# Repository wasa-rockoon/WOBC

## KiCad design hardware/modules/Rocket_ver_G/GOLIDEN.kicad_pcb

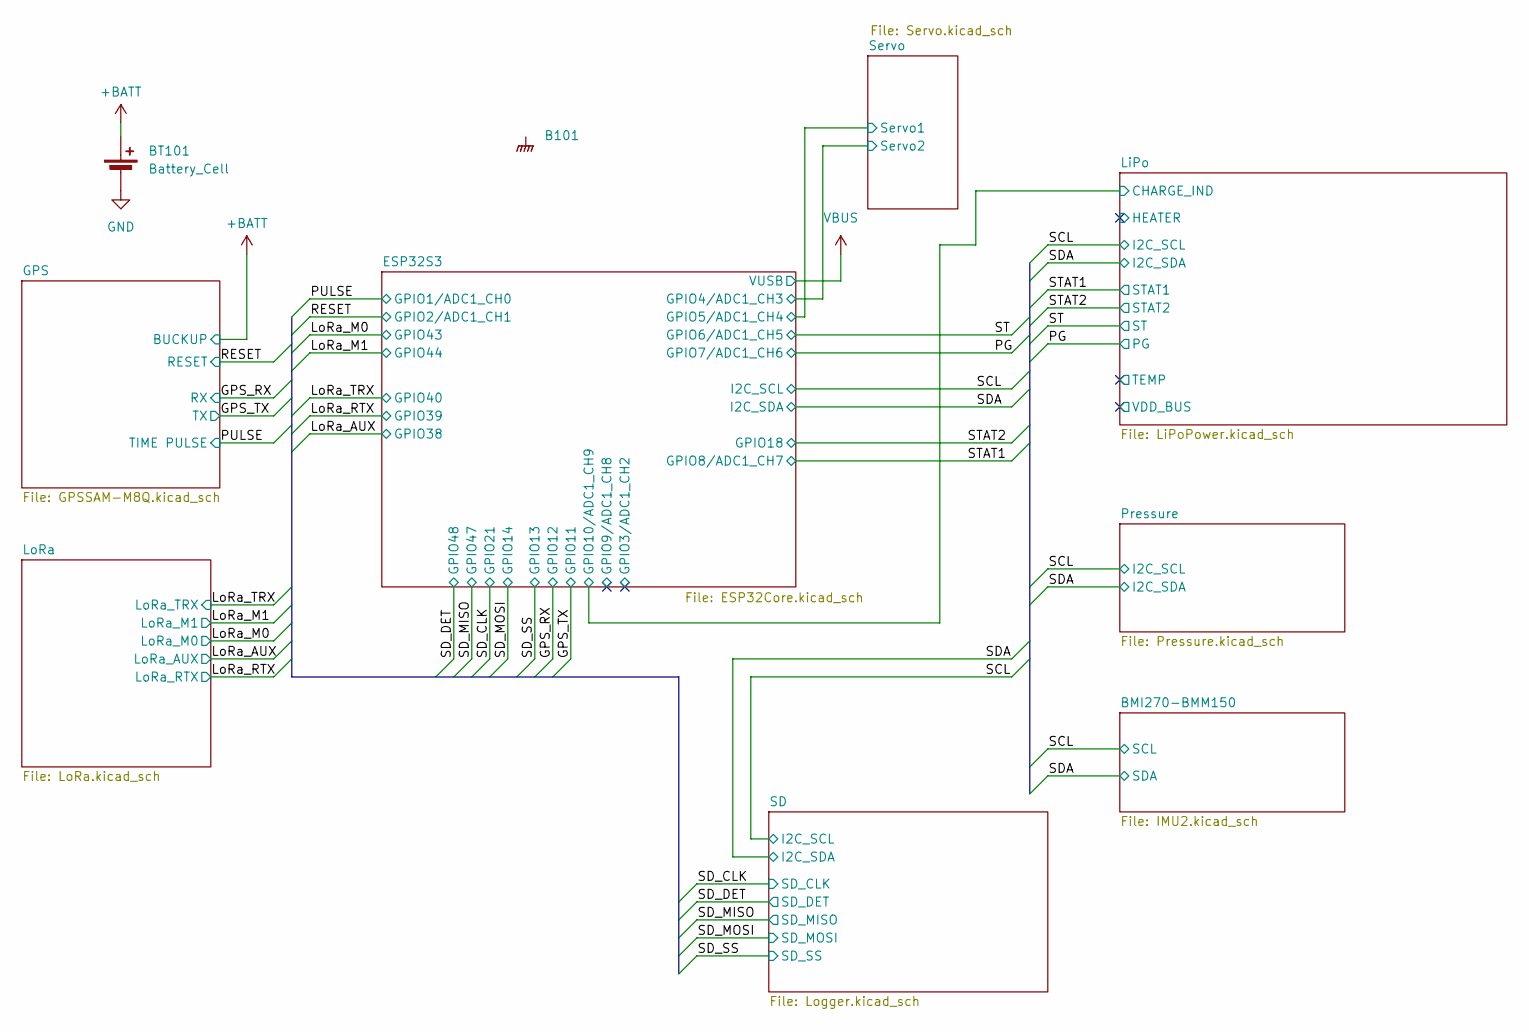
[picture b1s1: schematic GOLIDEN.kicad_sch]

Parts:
B101: Board_1U_40x120_for_Rocket
BT101: Battery_Cell; cr1220

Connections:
+BATT: BT101.1 (+); also elsewhere on the board
GND: B101.GND, BT101.2 (-); also elsewhere on the board

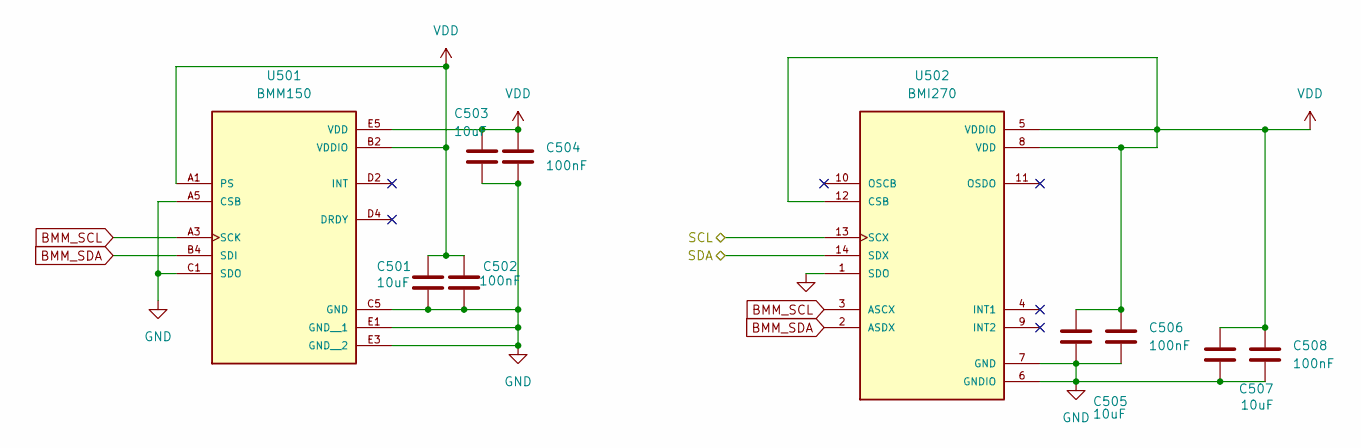
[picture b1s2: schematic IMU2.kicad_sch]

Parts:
C501, C503, C505, C507: 10uF; C_0603_1608Metric
C502, C504, C506, C508: 100nF; C_0402_1005Metric
U501: BMM150; XDCR_BMM150
U502: BMI270; XDCR_BMI270

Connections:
/SCL: U502.13 (SCX); also elsewhere on the board
/SDA: U502.14 (SDX); also elsewhere on the board
BMM_SCL: U501.A3 (SCK), U502.3 (ASCX)
BMM_SDA: U501.B4 (SDI), U502.2 (ASDX)
GND: C501.2, C502.2, C503.2, C504.2, C505.2, C506.2, C507.2, C508.2, U501.A5 (CSB), U501.C1 (SDO), U501.C5 (GND), U501.E1 (GND__1), U501.E3 (GND__2), U502.1 (SDO), U502.6 (GNDIO), U502.7 (GND); also elsewhere on the board
VDD: C501.1, C502.1, C503.1, C504.1, C505.1, C506.1, C507.1, C508.1, U501.A1 (PS), U501.B2 (VDDIO), U501.E5 (VDD), U502.5 (VDDIO), U502.8 (VDD), U502.12 (CSB); also elsewhere on the board

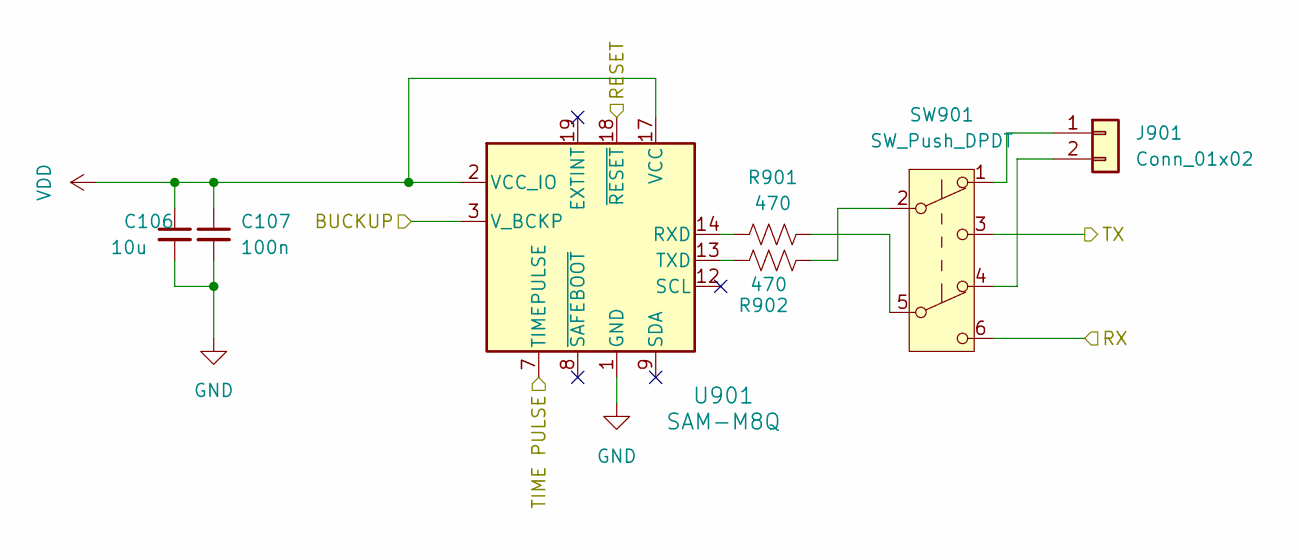
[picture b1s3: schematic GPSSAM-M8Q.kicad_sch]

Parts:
C106: 10u; C_0603_1608Metric; LCSC C96446
C107: 100n; C_0402_1005Metric; LCSC C1525
J901: Conn_01x02; PinHeader_1x02_P2.54mm_Vertical
R901, R902: 470; R_0402_1005Metric
SW901: SW_Push_DPDT; IS-2245S-G
U901: SAM-M8Q; ublox_SAM-M8Q

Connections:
+BATT: U901.3 (V_BCKP); also elsewhere on the board
/GPS_RX: SW901.6 (C); also elsewhere on the board
/GPS_TX: SW901.3 (C); also elsewhere on the board
/PULSE: U901.7 (TIMEPULSE); also elsewhere on the board
/RESET: U901.18 (~RESET); also elsewhere on the board
GND: C106.2, C107.2, U901.1 (GND), U901.4 (GND), U901.5 (GND), U901.6 (GND), U901.10 (GND), U901.11 (GND), U901.15 (GND), U901.16 (GND), U901.20 (GND); also elsewhere on the board
unnamed: J901.1, SW901.1 (A)
unnamed: J901.2, SW901.4 (A)
unnamed: R901.2, SW901.5 (B)
unnamed: R902.2, SW901.2 (B)
unnamed: R901.1, U901.14 (RXD)
unnamed: R902.1, U901.13 (TXD)
VDD: C106.1, C107.1, U901.2 (VCC_IO), U901.17 (VCC); also elsewhere on the board

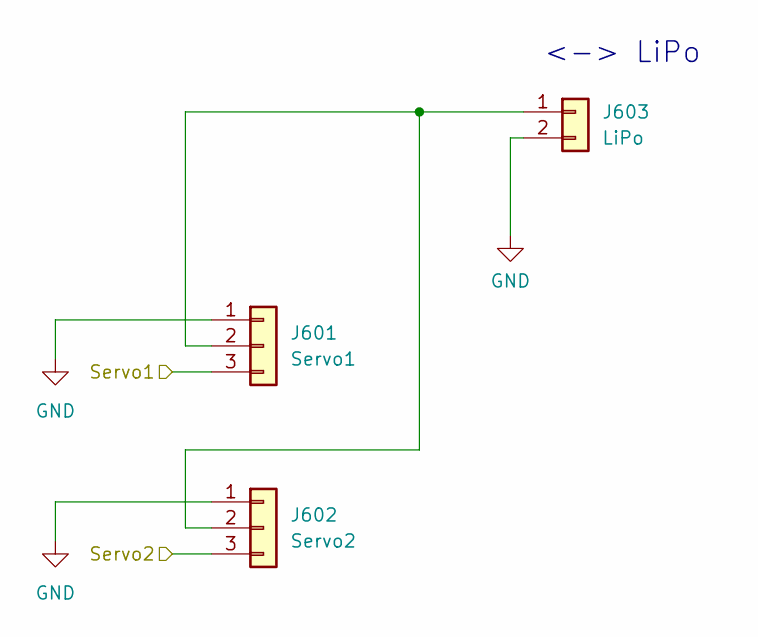
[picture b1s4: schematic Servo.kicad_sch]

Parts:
J601: Servo1; Harwin_M20-89003xx_1x03_P2.54mm_Horizontal
J602: Servo2; Harwin_M20-89003xx_1x03_P2.54mm_Horizontal
J603: LiPo; JST_PH_S2B-PH-K_1x02_P2.00mm_Horizontal

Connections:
/ESP32S3/GPIO4/ADC1_CH3: J602.3; also elsewhere on the board
/ESP32S3/GPIO5/ADC1_CH4: J601.3; also elsewhere on the board
GND: J601.1, J602.1, J603.2; also elsewhere on the board
unnamed: J601.2, J602.2, J603.1

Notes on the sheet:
<-> LiPo

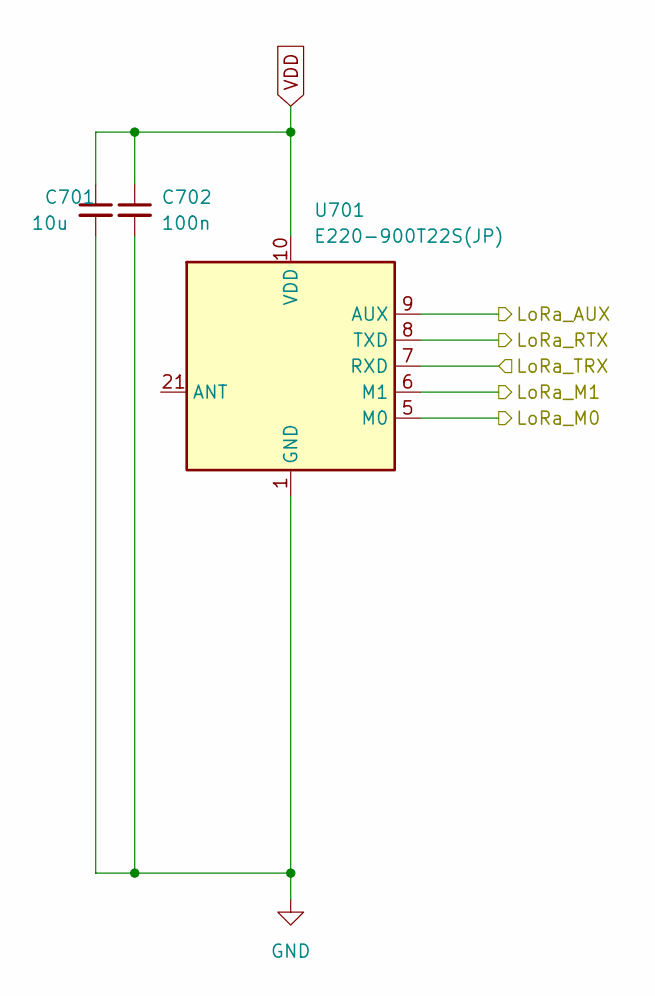
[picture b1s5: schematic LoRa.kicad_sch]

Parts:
C701: 10u; C_0603_1608Metric; LCSC C96446
C702: 100n; C_0402_1005Metric; LCSC C1525
U701: E220-900T22S(JP)

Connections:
/LoRa_AUX: U701.9 (AUX); also elsewhere on the board
/LoRa_M0: U701.5 (M0); also elsewhere on the board
/LoRa_M1: U701.6 (M1); also elsewhere on the board
/LoRa_RTX: U701.8 (TXD); also elsewhere on the board
/LoRa_TRX: U701.7 (RXD); also elsewhere on the board
GND: C701.2, C702.2, U701.1 (GND), U701.2 (GND), U701.3 (GND), U701.4 (GND), U701.11 (GND), U701.13 (GND), U701.19 (GND), U701.20 (GND), U701.22 (GND); also elsewhere on the board
VDD: C701.1, C702.1, U701.10 (VDD); also elsewhere on the board

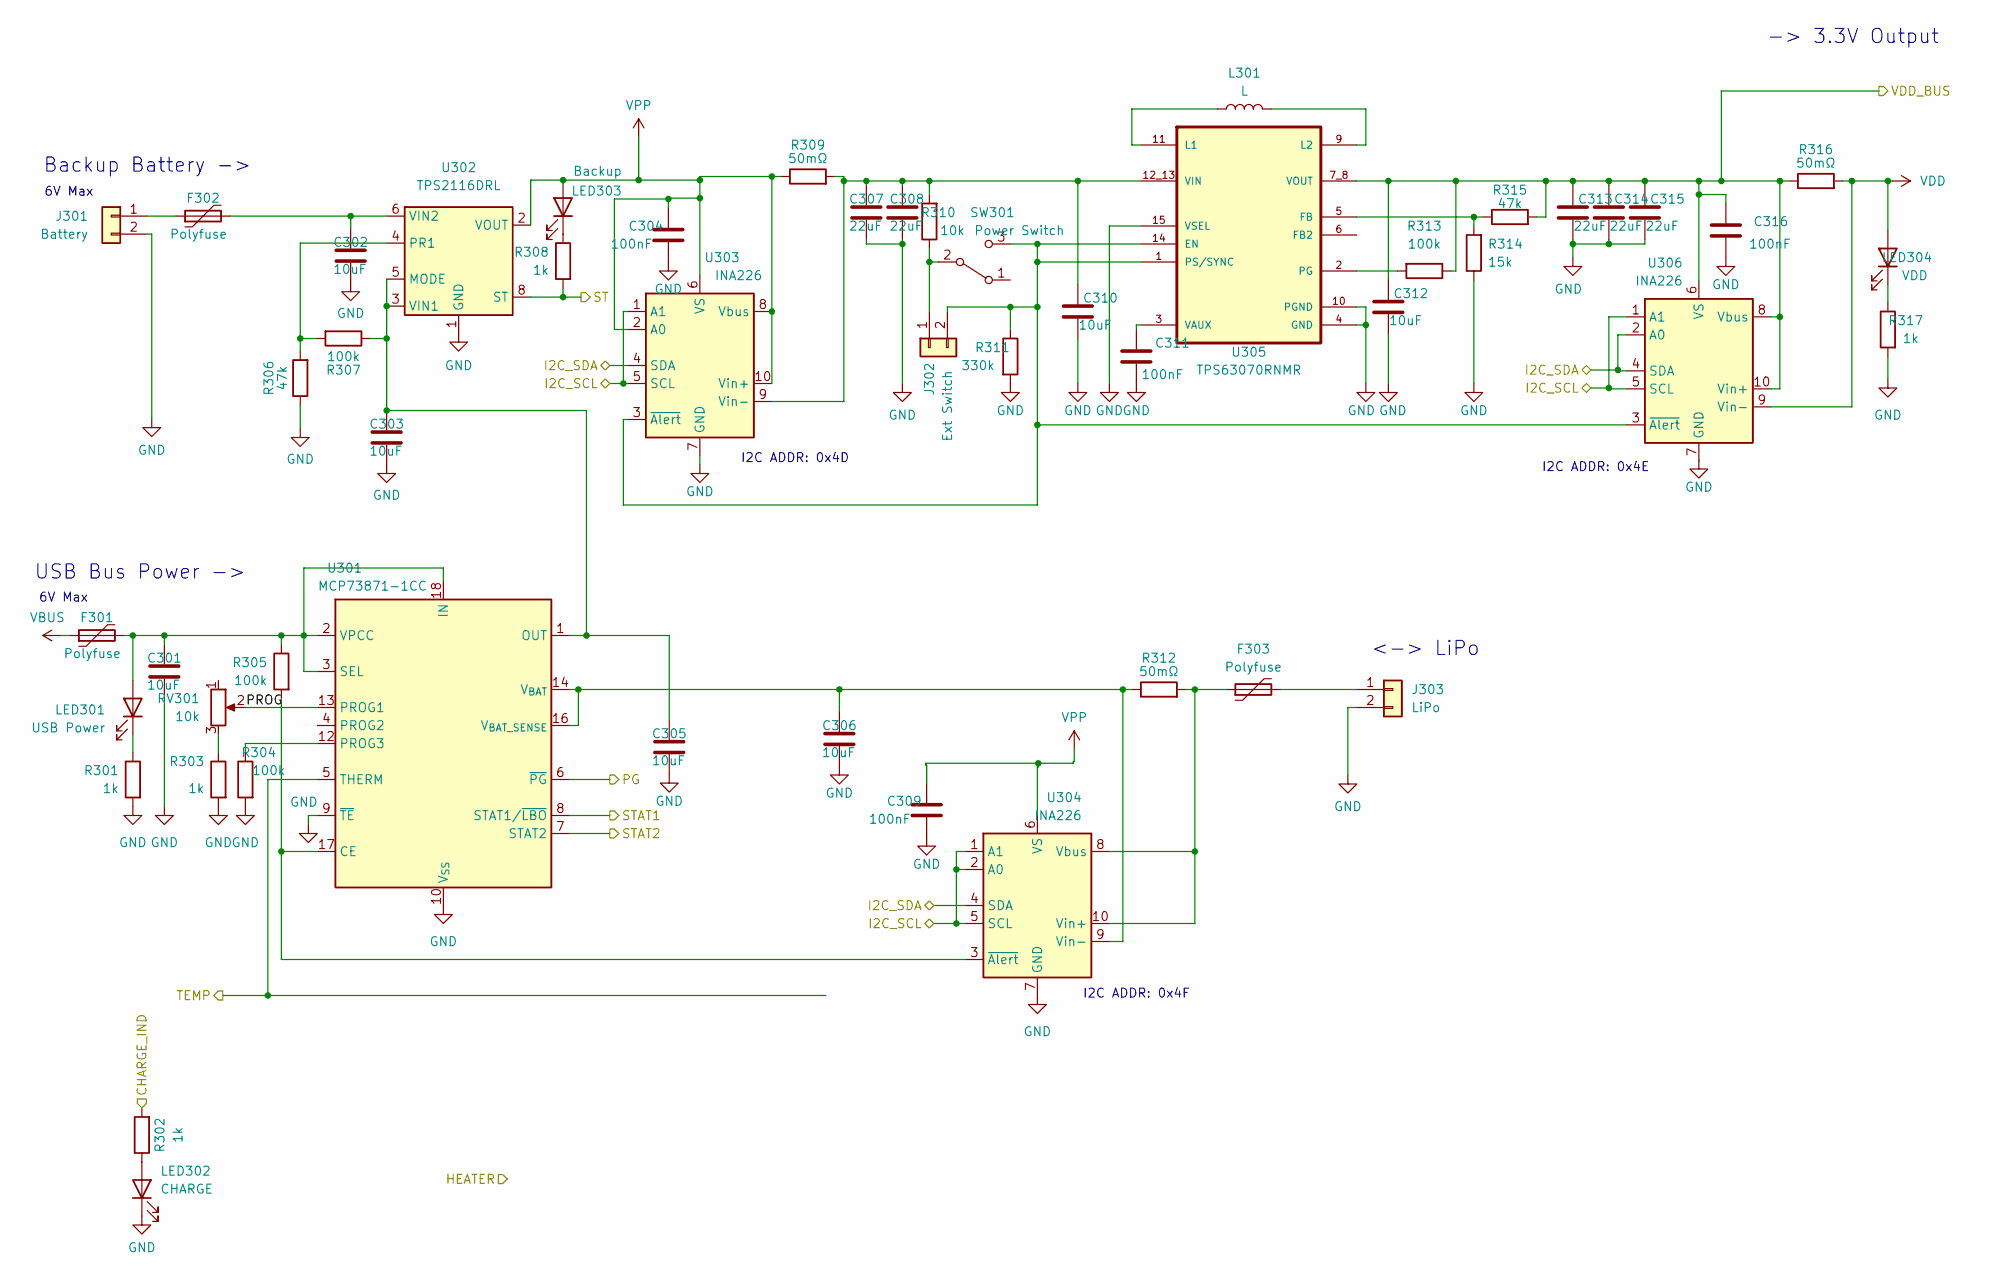
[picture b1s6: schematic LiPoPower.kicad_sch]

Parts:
C301, C302, C303, C305, C306, C310, C312: 10uF; C_0603_1608Metric; LCSC C96446
C304, C309, C311, C316: 100nF; C_0402_1005Metric; LCSC C1525
C307, C308, C313, C314, C315: 22uF; C_0805_2012Metric; LCSC C45783
F301, F302, F303: Polyfuse; Fuse_1206_3216Metric; LCSC C883133
J301: Battery; JST_XH_B2B-XH-A_1x02_P2.50mm_Vertical
J302: Ext Switch; JST_PH_S2B-PH-K_1x02_P2.00mm_Horizontal
J303: LiPo; JST_PH_S2B-PH-K_1x02_P2.00mm_Horizontal
L301: L; L_Wuerth_WE-TPC-3816; LCSC C3033018
LED301: USB Power; LED_0805_2012Metric; LCSC C2297
LED302: CHARGE; LED_0805_2012Metric; LCSC C2296
LED303: Backup; LED_0805_2012Metric; LCSC C2296
LED304: VDD; LED_0805_2012Metric; LCSC C2297
R301, R302, R303, R308, R317: 1k; R_0402_1005Metric; LCSC C11702
R304, R305, R307, R313: 100k; R_0402_1005Metric; LCSC C25741
R306, R315: 47k; R_0402_1005Metric; LCSC C25792
R309, R312, R316: 50mΩ; R_0805_2012Metric; LCSC C247602
R310: 10k; R_0402_1005Metric; LCSC C25744
R311: 330k; R_0402_1005Metric; LCSC C25778
R314: 15k; R_0402_1005Metric; LCSC C25756
RV301: 10k; Potentiometer_Bourns_TC33X_Vertical; LCSC C719176
SW301: Power Switch; SW_Slide_SPDT_Straight_CK_OS102011MS2Q
U301: MCP73871-1CC; QFN-20-1EP_4x4mm_P0.5mm_EP2.5x2.5mm; LCSC C511310
U302: TPS2116DRL; SOT-583-8
U303, U304, U306: INA226; VSSOP-10_3x3mm_P0.5mm; LCSC C49851
U305: TPS63070RNMR; VREG_TPS63070RNMR; LCSC C109322

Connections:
/ESP32S3/GPIO10/ADC1_CH9: R302.2; also elsewhere on the board
/LiPo/PROG: RV301.2, U301.13 (PROG1)
/LiPo/TEMP: U301.5 (THERM)
/LiPo/VDD_BUS: C312.1, C313.1, C314.1, C315.1, C316.1, R313.1, R315.2, R316.1, U305.7_8 (VOUT), U306.6 (VS), U306.8 (Vbus), U306.10 (Vin+)
/PG: U301.6 (~PG); also elsewhere on the board
/SCL: U303.1 (A1), U303.5 (SCL), U304.1 (A1), U304.2 (A0), U304.5 (SCL), U306.1 (A1), U306.5 (SCL); also elsewhere on the board
/SDA: U303.4 (SDA), U304.4 (SDA), U306.2 (A0), U306.4 (SDA); also elsewhere on the board
/ST: R308.2, U302.8 (ST); also elsewhere on the board
/STAT1: U301.8 (STAT1/~LBO); also elsewhere on the board
/STAT2: U301.7 (STAT2); also elsewhere on the board
GND: C301.2, C302.2, C303.2, C304.2, C305.2, C306.2, C307.2, C308.2, C309.2, C310.2, C311.2, C312.2, C313.2, C314.2, C315.2, C316.2, J301.2, J303.2, LED302.1 (K), R301.2, R303.2, R304.2, R306.1, R311.2, R314.1, R317.2, U301.9 (~TE), U301.10 (V_{SS}), U301.11 (V_{SS}), U301.21 (V_{SS}), U302.1 (GND), U303.7 (GND), U304.7 (GND), U305.4 (GND), U305.10 (PGND), U305.15 (VSEL), U306.7 (GND); also elsewhere on the board
unnamed: F302.1, J301.1
unnamed: J302.1, R310.1, SW301.2 (B)
unnamed: J302.2, R311.1, SW301.3 (C), U303.3 (~Alert), U305.1 (PS/SYNC), U305.14 (EN), U306.3 (~Alert)
unnamed: F303.2, J303.1
unnamed: C301.1, F301.2, LED301.2 (A), R305.1, U301.2 (VPCC), U301.3 (SEL), U301.18 (IN), U301.19 (IN)
unnamed: LED301.1 (K), R301.1
unnamed: LED302.2 (A), R302.1
unnamed: LED303.1 (K), R308.1
unnamed: LED304.1 (K), R317.1
unnamed: R303.1, RV301.3
unnamed: R305.2, U301.17 (CE), U304.3 (~Alert)
unnamed: R304.1, U301.12 (PROG3)
unnamed: C306.1, R312.1, U301.14 (V_{BAT}), U301.15 (V_{BAT}), U301.16 (V_{BAT_SENSE}), U304.9 (Vin-)
unnamed: C303.1, C305.1, R307.1, U301.1 (OUT), U301.20 (OUT), U302.3 (VIN1), U302.5 (MODE)
unnamed: R306.2, R307.2, U302.4 (PR1)
unnamed: C302.1, F302.2, U302.6 (VIN2)
unnamed: C307.1, C308.1, C310.1, R309.2, R310.2, U303.9 (Vin-), U305.12_13 (VIN)
unnamed: F303.1, R312.2, U304.8 (Vbus), U304.10 (Vin+)
unnamed: R314.2, R315.1, U305.5 (FB)
unnamed: L301.1, U305.11 (L1)
unnamed: L301.2, U305.9 (L2)
unnamed: R313.2, U305.2 (PG)
unnamed: C311.1, U305.3 (VAUX)
VBUS: F301.1; also elsewhere on the board
VDD: LED304.2 (A), R316.2, U306.9 (Vin-); also elsewhere on the board
VPP: C304.1, C309.1, LED303.2 (A), R309.1, U302.2 (VOUT), U302.7 (VOUT), U303.2 (A0), U303.6 (VS), U303.8 (Vbus), U303.10 (Vin+), U304.6 (VS)

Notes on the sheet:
6V Max
USB Bus Power ->
<-> LiPo
I2C ADDR: 0x4D
I2C ADDR: 0x4F
-> 3.3V Output
I2C ADDR: 0x4E
Backup Battery ->

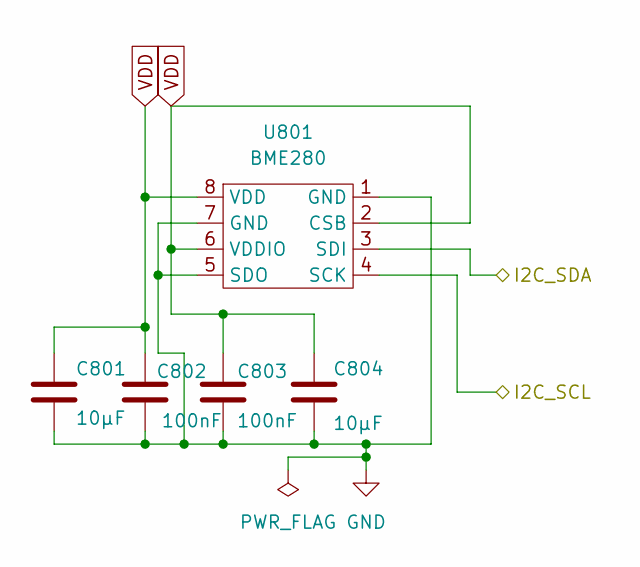
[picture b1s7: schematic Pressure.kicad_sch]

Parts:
C801, C804: 10μF; C_0603_1608Metric; LCSC C96446
C802, C803: 100nF; C_0402_1005Metric; LCSC C1525
U801: BME280; LCSC C92489

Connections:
/SCL: U801.4 (SCK); also elsewhere on the board
/SDA: U801.3 (SDI); also elsewhere on the board
GND: C801.2, C802.2, C803.2, C804.2, U801.1 (GND), U801.5 (SDO), U801.7 (GND); also elsewhere on the board
VDD: C801.1, C802.1, C803.1, C804.1, U801.2 (CSB), U801.6 (VDDIO), U801.8 (VDD); also elsewhere on the board

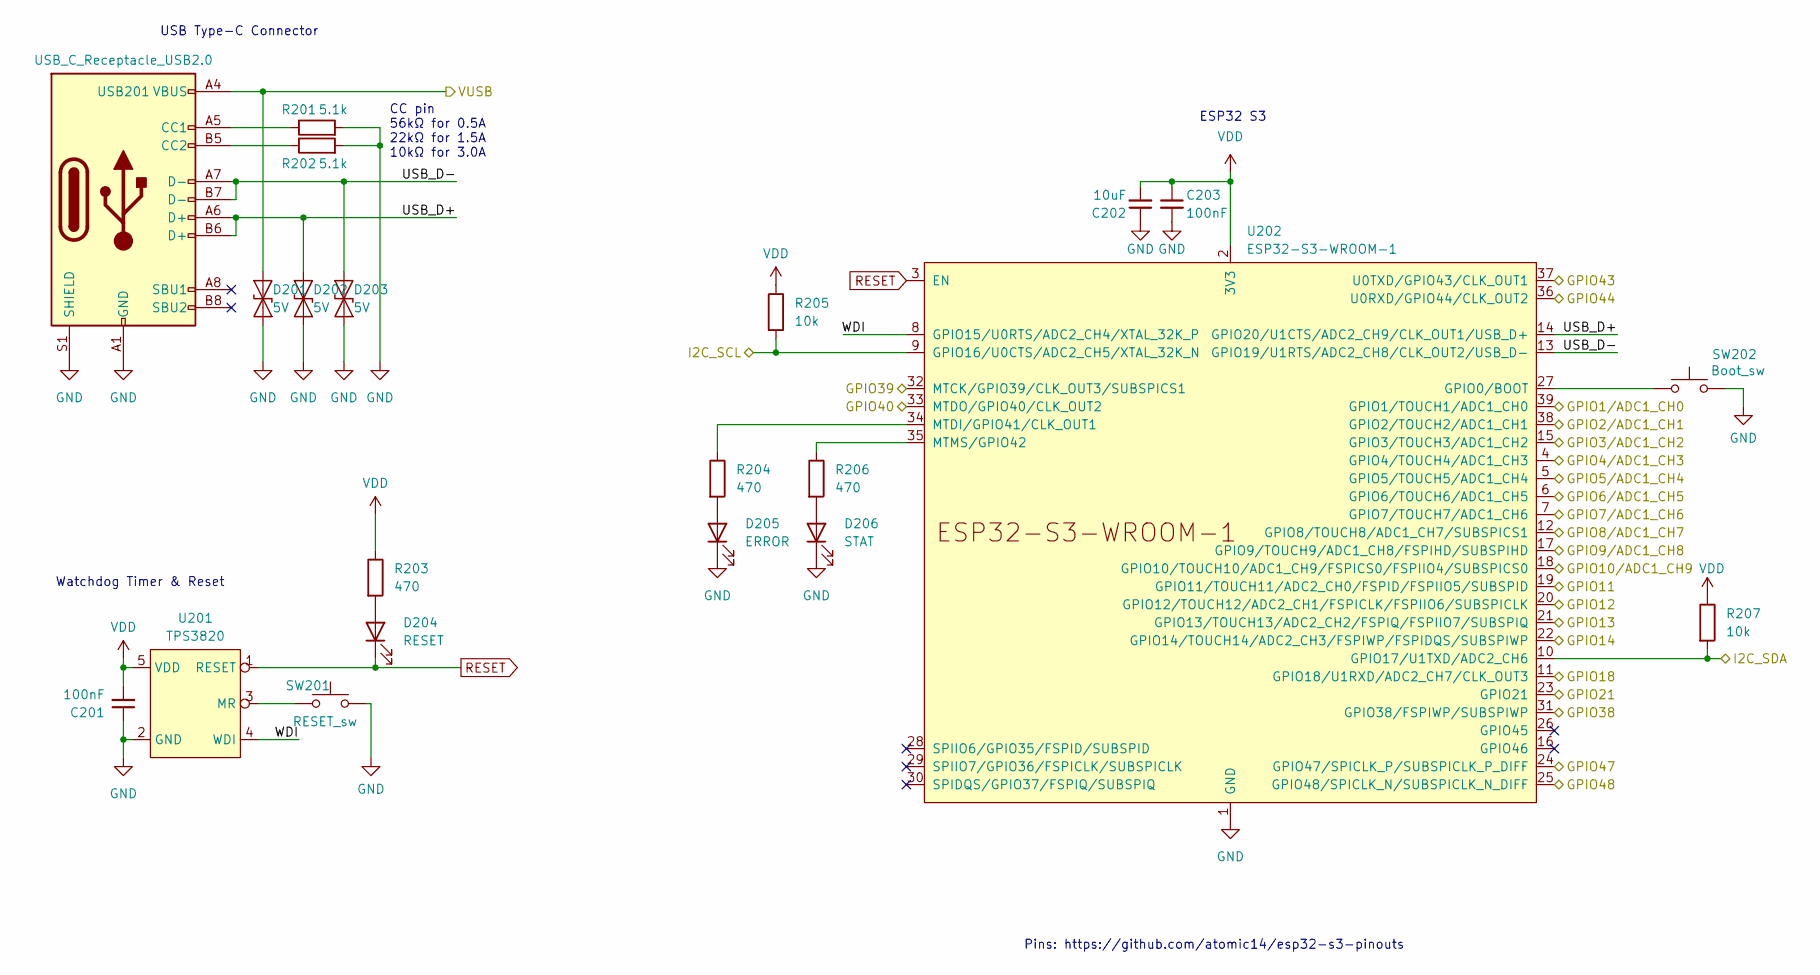
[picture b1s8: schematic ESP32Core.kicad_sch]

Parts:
C201, C203: 100nF; C_0402_1005Metric; LCSC C1525
C202: 10uF; C_0603_1608Metric; LCSC C96446
D201, D202, D203: 5V; D_SOD-882; LCSC C7420372
D204: RESET; LED_0805_2012Metric; LCSC C2296
D205: ERROR; LED_0805_2012Metric; LCSC C84256
D206: STAT; LED_0805_2012Metric; LCSC C2297
R201, R202: 5.1k; R_0402_1005Metric; LCSC C25905
R203, R204, R206: 470; R_0402_1005Metric; LCSC C25117
R205, R207: 10k; R_0402_1005Metric; LCSC C25744
SW201: RESET_sw; TVAF06-A020B-R
SW202: Boot_sw; TVAF06-A020B-R
U201: TPS3820; SOT-23-5; LCSC C7719
U202: ESP32-S3-WROOM-1
USB201: USB_C_Receptacle_USB2.0; USB_C_TYPEC-301S-ACP16X7; LCSC C2856766

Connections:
/ESP32S3/GPIO3/ADC1_CH2: U202.15 (GPIO3/TOUCH3/ADC1_CH2)
/ESP32S3/GPIO4/ADC1_CH3: U202.4 (GPIO4/TOUCH4/ADC1_CH3); also elsewhere on the board
/ESP32S3/GPIO5/ADC1_CH4: U202.5 (GPIO5/TOUCH5/ADC1_CH4); also elsewhere on the board
/ESP32S3/GPIO9/ADC1_CH8: U202.17 (GPIO9/TOUCH9/ADC1_CH8/FSPIHD/SUBSPIHD)
/ESP32S3/GPIO10/ADC1_CH9: U202.18 (GPIO10/TOUCH10/ADC1_CH9/FSPICS0/FSPIIO4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); also elsewhere on the board
/ESP32S3/USB_D+: D202.2 (A2), U202.14 (GPIO20/U1CTS/ADC2_CH9/CLK_OUT1/USB_D+), USB201.A6 (D+), USB201.B6 (D+)
/ESP32S3/USB_D-: D203.2 (A2), U202.13 (GPIO19/U1RTS/ADC2_CH8/CLK_OUT2/USB_D-), USB201.A7 (D-), USB201.B7 (D-)
/ESP32S3/WDI: U201.4 (WDI), U202.8 (GPIO15/U0RTS/ADC2_CH4/XTAL_32K_P)
/GPS_RX: U202.20 (GPIO12/TOUCH12/ADC2_CH1/FSPICLK/FSPIIO6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); also elsewhere on the board
/GPS_TX: U202.19 (GPIO11/TOUCH11/ADC2_CH0/FSPID/FSPIIO5/S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); also elsewhere on the board
/LoRa_AUX: U202.31 (GPIO38/FSPIWP/SUBSPIWP); also elsewhere on the board
/LoRa_M0: U202.37 (U0TXD/GPIO43/CLK_OUT1); also elsewhere on the board
/LoRa_M1: U202.36 (U0RXD/GPIO44/CLK_OUT2); also elsewhere on the board
/LoRa_RTX: U202.32 (MTCK/GPIO39/CLK_OUT3/SUBSPICS1); also elsewhere on the board
/LoRa_TRX: U202.33 (MTDO/GPIO40/CLK_OUT2); also elsewhere on the board
/PG: U202.7 (GPIO7/TOUCH7/ADC1_CH6); also elsewhere on the board
/PULSE: U202.39 (GPIO1/TOUCH1/ADC1_CH0); also elsewhere on the board
/RESET: U202.38 (GPIO2/TOUCH2/ADC1_CH1); also elsewhere on the board
/SCL: R205.2, U202.9 (GPIO16/U0CTS/ADC2_CH5/XTAL_32K_N); also elsewhere on the board
/SDA: R207.2, U202.10 (GPIO17/U1TXD/ADC2_CH6); also elsewhere on the board
/SD_CLK: U202.23 (GPIO21); also elsewhere on the board
/SD_DET: U202.25 (GPIO48/SPICLK_N/SUBSPICLK_N_DIFF); also elsewhere on the board
/SD_MISO: U202.24 (GPIO47/SPICLK_P/SUBSPICLK_P_DIFF); also elsewhere on the board
/SD_MOSI: U202.22 (GPIO14/TOUCH14/ADC2_CH3/FSPIWP/FSPIDQS/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); also elsewhere on the board
/SD_SS: U202.21 (GPIO13/TOUCH13/ADC2_CH2/FSPIQ/FSPIIO7/S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); also elsewhere on the board
/ST: U202.6 (GPIO6/TOUCH6/ADC1_CH5); also elsewhere on the board
/STAT1: U202.12 (GPIO8/TOUCH8/ADC1_CH7/SUBSPICS1); also elsewhere on the board
/STAT2: U202.11 (GPIO18/U1RXD/ADC2_CH7/CLK_OUT3); also elsewhere on the board
GND: C201.1, C202.1, C203.2, D201.1 (A1), D202.1 (A1), D203.1 (A1), D205.1 (K), D206.1 (K), R201.2, R202.2, SW201.2, SW202.2, U201.2 (GND), U202.1 (GND), U202.40 (GND), U202.41 (GND), USB201.A1 (GND), USB201.A12 (GND), USB201.B1 (GND), USB201.B12 (GND), USB201.S1 (SHIELD); also elsewhere on the board
unnamed: D204.2 (A), R203.2
unnamed: D205.2 (A), R204.2
unnamed: D206.2 (A), R206.2
unnamed: SW201.1, U201.3 (MR)
unnamed: SW202.1, U202.27 (GPIO0/BOOT)
unnamed: R204.1, U202.34 (MTDI/GPIO41/CLK_OUT1)
unnamed: R206.1, U202.35 (MTMS/GPIO42)
unnamed: R201.1, USB201.A5 (CC1)
unnamed: R202.1, USB201.B5 (CC2)
RESET: D204.1 (K), U201.1 (RESET), U202.3 (EN)
VBUS: D201.2 (A2), USB201.A4 (VBUS), USB201.A9 (VBUS), USB201.B4 (VBUS), USB201.B9 (VBUS); also elsewhere on the board
VDD: C201.2, C202.2, C203.1, R203.1, R205.1, R207.1, U201.5 (VDD), U202.2 (3V3); also elsewhere on the board

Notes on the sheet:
ESP32 S3
Watchdog Timer & Reset
Pins: https://github.com/atomic14/esp32-s3-pinouts
USB Type-C Connector
CC pin 56kΩ for 0.5A 22kΩ for 1.5A 10kΩ for 3.0A

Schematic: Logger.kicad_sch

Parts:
C401: 10uF; C_0402_1005Metric; LCSC C96446
C402: 100nF; C_0402_1005Metric; LCSC C1525
D401, D402: D; D_SOD-323; LCSC C191023
MICRO_SD401: TF-01A; LCSC C5155563
U401: PCF8563T; SOIC-8_3.9x4.9mm_P1.27mm; LCSC C7440
Y401: Crystal; Crystal_SMD_3215-2Pin_3.2x1.5mm; LCSC C32346

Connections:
+BATT: D401.2 (A); also elsewhere on the board
/SCL: U401.6 (SCL); also elsewhere on the board
/SDA: U401.5 (SDA); also elsewhere on the board
/SD_CLK: MICRO_SD401.5 (CLK); also elsewhere on the board
/SD_DET: MICRO_SD401.CD1 (CD); also elsewhere on the board
/SD_MISO: MICRO_SD401.7 (DAT0); also elsewhere on the board
/SD_MOSI: MICRO_SD401.3 (CMD); also elsewhere on the board
/SD_SS: MICRO_SD401.2 (CD/DAT3); also elsewhere on the board
GND: C401.2, C402.1, MICRO_SD401.6 (VSS), MICRO_SD401.MP1 (SHIELD), MICRO_SD401.MP2 (SHIELD), MICRO_SD401.MP3 (SHIELD), MICRO_SD401.MP4 (SHIELD), U401.4 (VSS); also elsewhere on the board
unnamed: C402.2, D401.1 (K), D402.1 (K), U401.8 (VDD)
unnamed: U401.1 (OSCI), Y401.1
unnamed: U401.2 (OSCO), Y401.2
VDD: C401.1, D402.2 (A), MICRO_SD401.4 (VDD); also elsewhere on the board

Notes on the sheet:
RTC
Micro SD Card Slot
I2C ADDR: 0x51

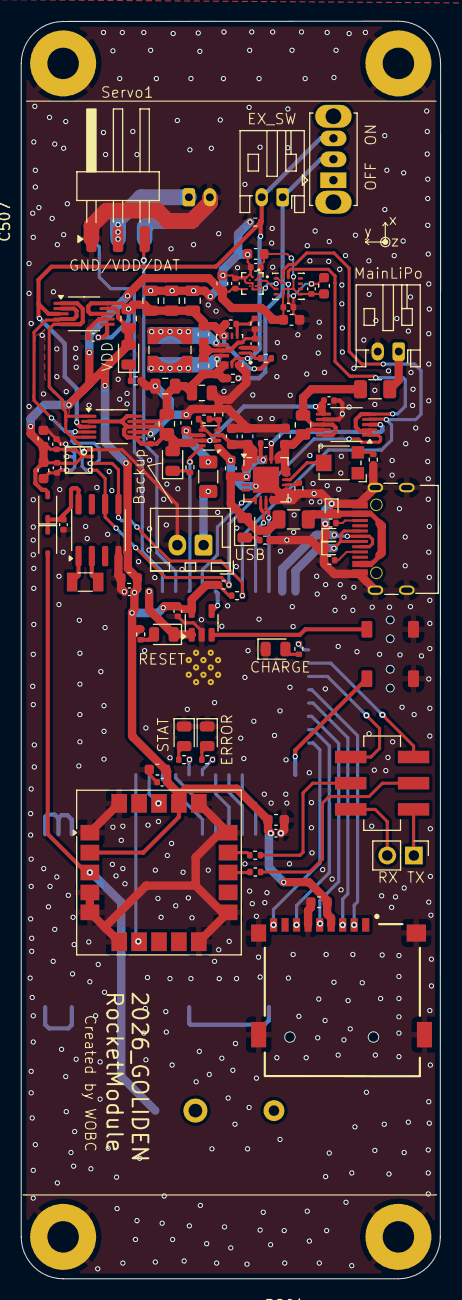
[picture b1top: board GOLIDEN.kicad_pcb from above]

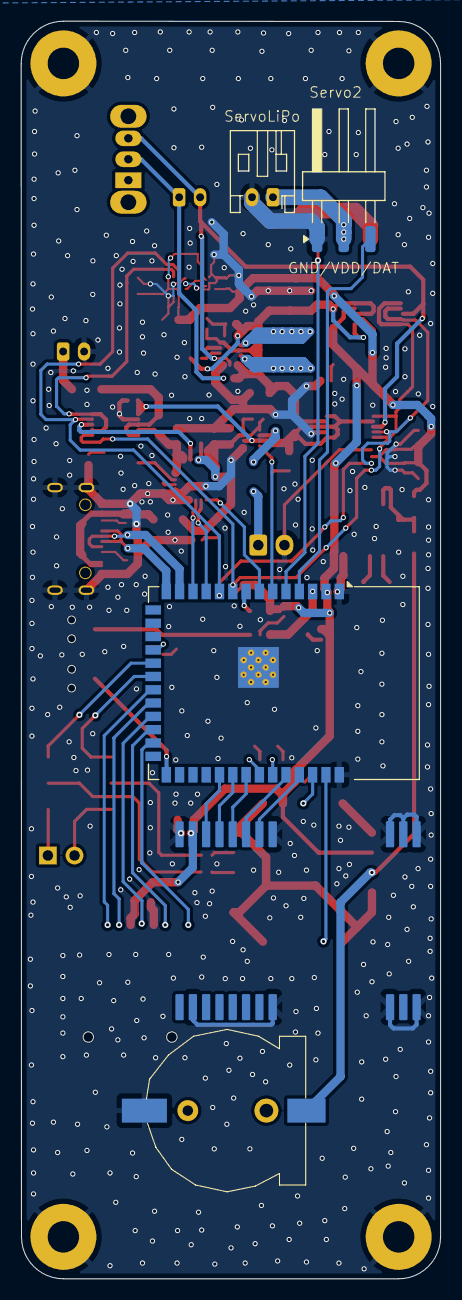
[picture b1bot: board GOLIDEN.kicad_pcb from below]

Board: 2 copper layers, 40.0 x 120.0 mm, 110 parts (5 on the bottom side), 78 nets.

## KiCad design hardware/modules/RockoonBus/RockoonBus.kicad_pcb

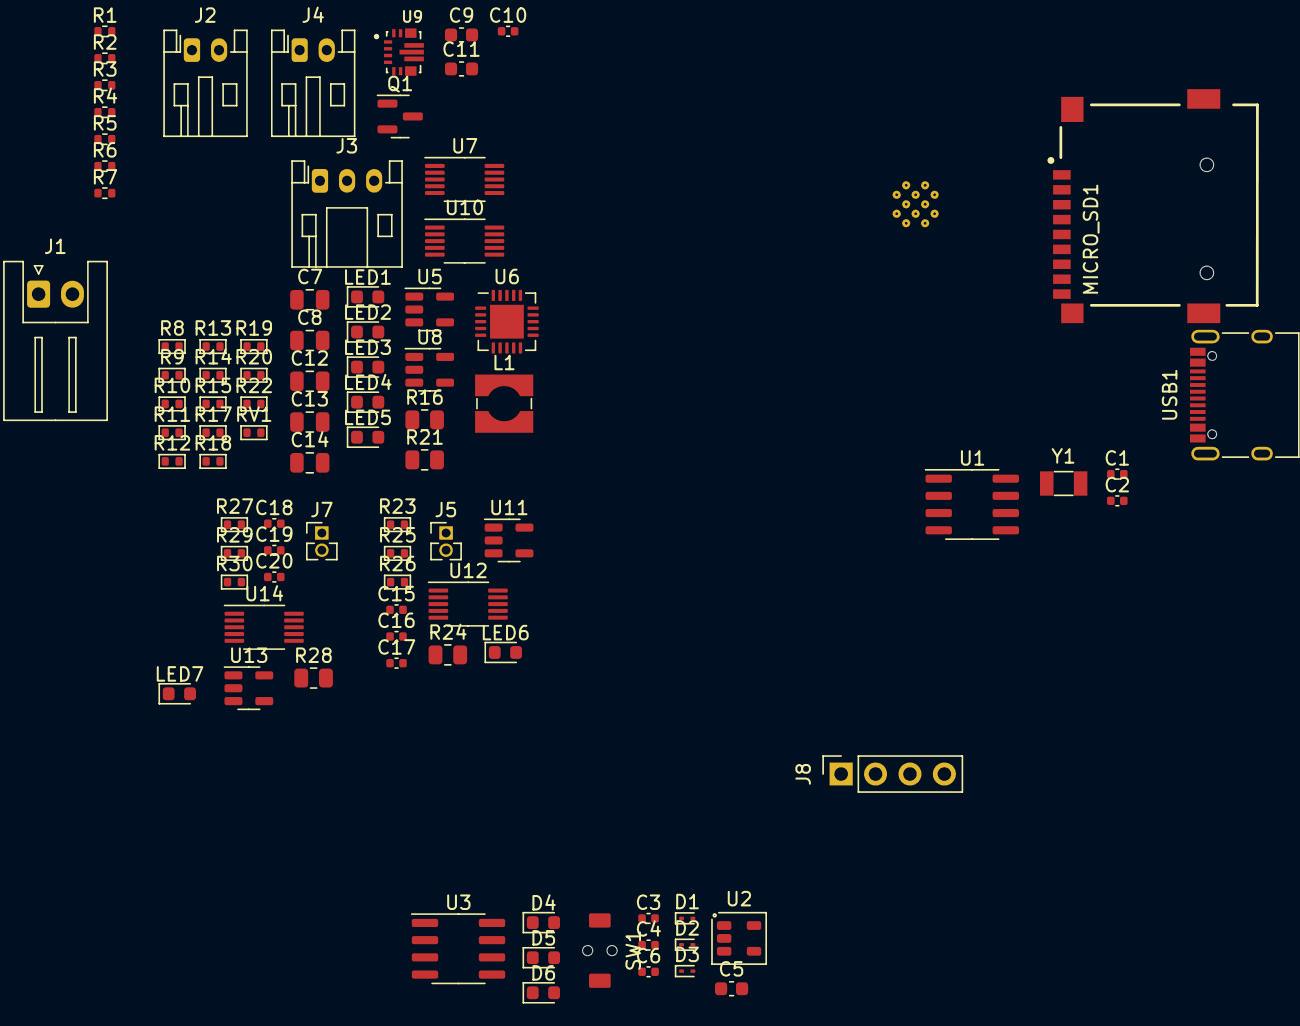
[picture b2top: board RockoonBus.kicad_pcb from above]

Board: 2 copper layers, 91 parts (1 on the bottom side), 66 nets, no tracks yet.

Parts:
C1: 10uF; C_0402_1005Metric
C2, C3, C4, C6, C10, C15, C16, C17, C18, C19, C20: 100nF; C_0402_1005Metric
C5, C9, C11: 10uF; C_0603_1608Metric
C7, C8, C12, C13, C14: 10uF; C_0805_2012Metric
D1, D2, D3: 5V; D_SOD-923
D4: RESET; LED_0603_1608Metric
D5: ERROR; LED_0603_1608Metric
D6: STAT; LED_0603_1608Metric
J1: Battery; JST_XH_S2B-XH-A_1x02_P2.50mm_Horizontal
J2: Ext Switch; JST_PH_S2B-PH-K_1x02_P2.00mm_Horizontal
J3: Temp&Heater; JST_PH_S3B-PH-K_1x03_P2.00mm_Horizontal
J4: LiPo; JST_PH_S2B-PH-K_1x02_P2.00mm_Horizontal
J5, J7: Jumper; PinHeader_1x02_P1.27mm_Vertical
J8: Conn_01x04; PinSocket_1x04_P2.54mm_Vertical
L1: L; L_Wuerth_WE-TPC-3816
LED1: USB Power; LED_0603_1608Metric
LED2: Backup Power; LED_0603_1608Metric
LED3: CHARGE; LED_0603_1608Metric
LED4: Heater; LED_0603_1608Metric
LED5: VDD; LED_0603_1608Metric
LED6, LED7: Power; LED_0603_1608Metric
MICRO_SD1: TF-01A
Q1: Q_NPN_BEC; SOT-23
R1, R2: 22k; R_0402_1005Metric
R3, R4, R6: 470; R_0402_1005Metric
R5, R7, R13, R23, R27: 10k; R_0402_1005Metric
R8, R9, R12, R14, R17, R22, R25, R29: 1k; R_0402_1005Metric
R10, R11: 47k; R_0402_1005Metric
R15, R18: 100k; R_0402_1005Metric
R16, R21, R24, R28: 50mΩ; R_0805_2012Metric
R19: 150k; R_0402_1005Metric
R20: 470k; R_0402_1005Metric
R26, R30: 120; R_0402_1005Metric
RV1: 20k; R_0402_1005Metric
SW1: RESET; TVAF06-A020B-R
U1: PCF8563T; SOIC-8_3.9x4.9mm_P1.27mm
U2: TPS3820; SOT-23-5
U3: SN65HVD230; SOIC-8_3.9x4.9mm_P1.27mm
U4: ESP32-S3-WROOM-1
U5, U8: SOT-23-5
U6: MCP73871-1CC; QFN-20-1EP_4x4mm_P0.5mm_EP2.5x2.5mm
U7, U10, U12, U14: INA226; VSSOP-10_3x3mm_P0.5mm
U9: TPS63070RNMR; VREG_TPS63070RNMR
U11, U13: TCK106AF; SOT-23-5
USB1: USB_C_Receptacle_USB2.0; USB_C_Receptacle_XKB_U262-16XN-4BVC11
Y1: Crystal; Crystal_SMD_3215-2Pin_3.2x1.5mm

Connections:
+BATT: C2.2, U1.8 (VDD)
/ESP32Core/CAN_RX: U3.4 (R), U4.36 (U0RXD/GPIO44/CLK_OUT2)
/ESP32Core/CAN_TX: U3.1 (D), U4.37 (U0TXD/GPIO43/CLK_OUT1)
/ESP32Core/I2C_SCL: R5.2, U4.9 (GPIO16/U0CTS/ADC2_CH5/XTAL_32K_N)
/ESP32Core/I2C_SDA: R7.2, U4.10 (GPIO17/U1TXD/ADC2_CH6)
/ESP32Core/USB_D+: D2.2 (A2), U4.14 (GPIO20/U1CTS/ADC2_CH9/CLK_OUT1/USB_D+), USB1.A6 (D+), USB1.B6 (D+)
/ESP32Core/USB_D-: D3.2 (A2), U4.13 (GPIO19/U1RTS/ADC2_CH8/CLK_OUT2/USB_D-), USB1.A7 (D-), USB1.B7 (D-)
/ESP32Core/WDI: U2.4 (WDI), U4.8 (GPIO15/U0RTS/ADC2_CH4/XTAL_32K_P)
/LiPoPower/I2C_SCL: U7.1 (A1), U7.2 (A0), U7.5 (SCL), U10.1 (A1), U10.5 (SCL)
/LiPoPower/I2C_SDA: U7.4 (SDA), U10.2 (A0), U10.4 (SDA)
/LiPoPower/PG: Q1.1 (B), R11.1, U5.3 (CONTROL), U6.6 (~PG)
/LiPoPower/TEMP: J3.2, U6.5 (THERM)
/LiPoPower/VDD_BUS: C11.1, C12.1, C13.1, C14.1, R18.1, R20.2, R21.1, U9.7_8 (VOUT), U10.8 (Vbus), U10.10 (Vin+)
/ModuleIF_A/I2C_SDA: U12.1 (A1), U12.4 (SDA)
/ModuleIF_A/VIN: C15.2, U11.5 (VIN)
/ModuleIF_S/CANH: J8.1, R30.2
/ModuleIF_S/CANL: J7.2, J8.2
/ModuleIF_S/I2C_SDA: U14.1 (A1), U14.4 (SDA)
/ModuleIF_S/VIN: C18.2, U13.5 (VIN)
GND: C1.2, C2.1, C3.1, C4.1, C5.1, C6.2, C7.2, C8.2, C9.2, C10.2, C11.2, C12.2, C13.2, C14.2, C15.1, C16.1, C17.1, C18.1, C19.1, C20.1, D1.1 (A1), D2.1 (A1), D3.1 (A1), D5.1 (K), D6.1 (K), J1.2, J3.3, J4.2, J8.4, LED3.1 (K), LED6.1 (K), LED7.1 (K), MICRO_SD1.6 (VSS), MICRO_SD1.MP1 (SHIELD), MICRO_SD1.MP2 (SHIELD), MICRO_SD1.MP3 (SHIELD), MICRO_SD1.MP4 (SHIELD), Q1.2 (E), R1.2, R2.2, R8.2, R9.2, R10.2, R15.2, R17.2, R19.1, R22.2, SW1.2, U1.4 (VSS), U2.2 (GND), U3.2 (GND), U3.8 (Rs), U4.1 (GND), U4.40 (GND), U4.41 (GND), U5.2 (GND), U6.9 (~TE), U6.10 (V_{SS}), U6.11 (V_{SS}), U6.21 (V_{SS}), U7.7 (GND), U8.2 (GND), U9.4 (GND), U9.10 (PGND), U9.15 (VSEL), U10.7 (GND), U11.2 (GND), U12.7 (GND), U13.2 (GND), U14.7 (GND), USB1.A1 (GND), USB1.A12 (GND), USB1.B1 (GND), USB1.B12 (GND), USB1.S1 (SHIELD)
NC: U5.4 (NC), U8.4 (NC), U11.4 (NC), U13.4 (NC)
unnamed: D4.2 (A), R3.2
unnamed: D5.2 (A), R4.2
unnamed: D6.2 (A), R6.2
unnamed: J2.1, R13.2
unnamed: J2.2, R15.1, U9.1 (PS/SYNC), U9.14 (EN), U10.3 (~Alert)
unnamed: J3.1, LED4.2 (A), U8.1 (VOUT)
unnamed: J5.1, R26.1
unnamed: R24.2, R25.2, U12.9 (Vin-)
unnamed: J7.1, R30.1
unnamed: J8.3, R28.2, R29.2, U14.9 (Vin-)
unnamed: LED1.2 (A), U6.2 (VPCC), U6.3 (SEL), U6.18 (IN), U6.19 (IN)
unnamed: LED1.1 (K), R8.1
unnamed: LED2.2 (A), R12.1
unnamed: LED2.1 (K), Q1.3 (C)
unnamed: LED3.2 (A), R14.1
unnamed: LED4.1 (K), R17.1
unnamed: LED5.1 (K), R22.1
unnamed: LED6.2 (A), R25.1
unnamed: LED7.2 (A), R29.1
unnamed: U1.1 (OSCI), Y1.1
unnamed: U1.2 (OSCO), Y1.2
unnamed: SW1.1, U2.3 (MR)
unnamed: R4.1, U4.34 (MTDI/GPIO41/CLK_OUT1)
unnamed: R6.1, U4.35 (MTMS/GPIO42)
unnamed: R11.2, U5.5 (VIN)
unnamed: U6.17 (CE), U7.3 (~Alert)
unnamed: RV1.2, U6.13 (PROG1)
unnamed: R10.1, U6.12 (PROG3)
unnamed: R16.1, U6.14 (V_{BAT}), U6.15 (V_{BAT}), U6.16 (V_{BAT_SENSE}), U7.6 (VS), U7.9 (Vin-)
unnamed: R16.2, U7.8 (Vbus), U7.10 (Vin+)
unnamed: R19.2, R20.1, U9.5 (FB)
unnamed: L1.1, U9.11 (L1)
unnamed: L1.2, U9.9 (L2)
unnamed: R18.2, U9.2 (PG)
unnamed: C10.1, U9.3 (VAUX)
unnamed: C7.1, C8.1, C9.1, R12.2, R13.1, U5.1 (VOUT), U6.1 (OUT), U6.20 (OUT), U8.5 (VIN), U9.12_13 (VIN), U10.6 (VS)
unnamed: R23.2, U11.3 (CONTROL), U12.3 (~Alert)
unnamed: C16.2, R24.1, U11.1 (VOUT), U12.8 (Vbus), U12.10 (Vin+)
unnamed: R27.2, U13.3 (CONTROL), U14.3 (~Alert)
unnamed: C19.2, R28.1, U13.1 (VOUT), U14.8 (Vbus), U14.10 (Vin+)
unnamed: R1.1, USB1.A5 (CC1)
unnamed: R2.1, USB1.B5 (CC2)
RESET: D4.1 (K), U2.1 (RESET), U4.3 (EN)
VBUS: D1.2 (A2), USB1.A4 (VBUS), USB1.A9 (VBUS), USB1.B4 (VBUS), USB1.B9 (VBUS)
VDD: C1.1, C3.2, C4.2, C5.2, C6.1, C17.2, C20.2, LED5.2 (A), MICRO_SD1.4 (VDD), R3.1, R5.1, R7.1, R21.2, U2.5 (VDD), U3.3 (VCC), U4.2 (3V3), U10.9 (Vin-), U12.6 (VS), U14.6 (VS)
